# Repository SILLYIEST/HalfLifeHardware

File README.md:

# Heartbie

Mini pet that you can interact with! 
(Based off of the starter project Starbie)

This was so fun to create! I love doing personal projects (despite having no prior experience here T-T)

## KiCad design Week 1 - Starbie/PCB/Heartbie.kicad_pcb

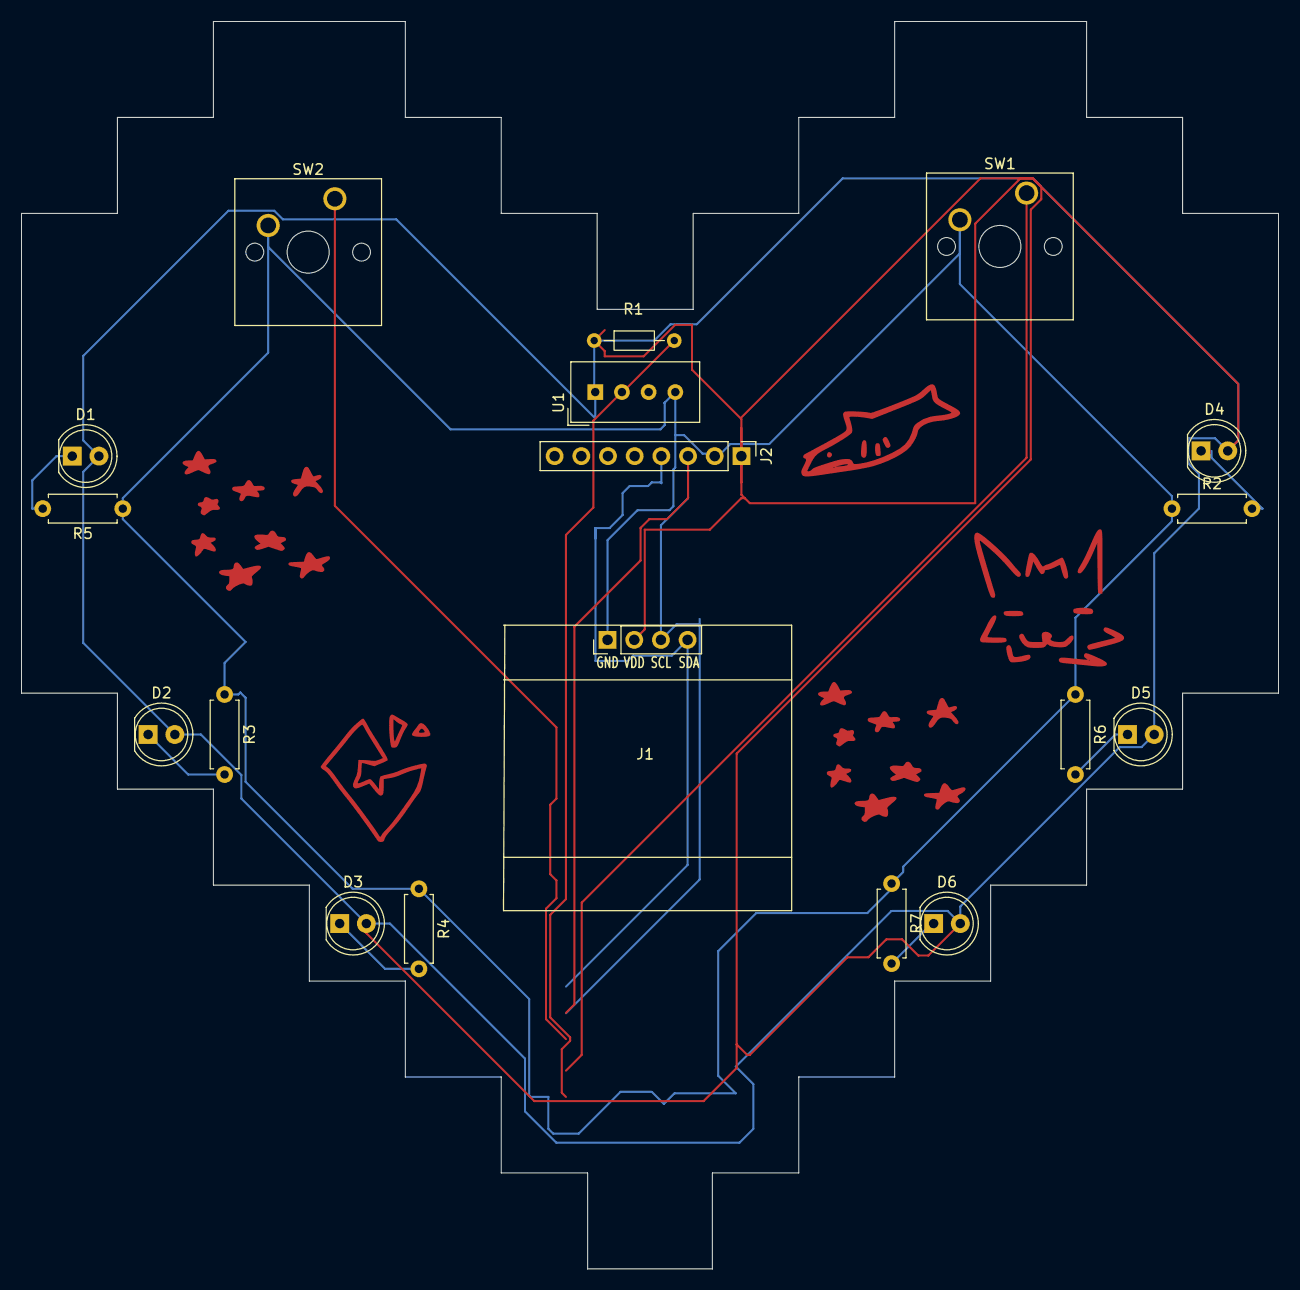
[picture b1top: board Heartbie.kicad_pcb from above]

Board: 2 copper layers, 119.7 x 118.8 mm, 19 parts (1 on the bottom side), 11 nets.

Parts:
D1, D2, D3, D4, D5, D6: LED; LED_D5.0mm
J1: Conn_01x04_Pin; Display_128x64_096_I2C
J2: Conn_01x08_Pin; PinHeader_1x08_P2.54mm_Vertical
R1: 10K; R_Axial_DIN0204_L3.6mm_D1.6mm_P7.62mm_Horizontal
R2, R3, R4, R5, R6, R7: R; R_Axial_DIN0207_L6.3mm_D2.5mm_P7.62mm_Horizontal
SW1, SW2: SW_Push; SW_Cherry_MX_1.00u_PCB
U1: DHT11; Aosong_DHT11_5.5x12.0_P2.54mm
U2: XIAO-ESP32-C3-SMD

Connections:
+3.3V: D1.2 (A), D2.2 (A), D3.2 (A), D4.2 (A), D5.2 (A), D6.2 (A), J1.2, J2.1, R1.1, U1.1 (VDD), U2.12 (3V3_OUT)
/DHT11 DATA: R1.2, U1.2 (DATA)
/SCL: J1.3, J2.3, U2.5 (D4)
/SDA: J1.4, J2.4, U2.6 (D5)
GND: J1.1, J2.2, R2.1, R3.1, R4.1, R5.1, R6.1, R7.1, SW1.2, SW2.2, U1.4 (GND), U2.13 (GND), U2.18 (GND)
unnamed: D1.1 (K), R5.2
unnamed: D2.1 (K), R3.2
unnamed: D3.1 (K), R4.2
unnamed: D4.1 (K), R2.2
unnamed: D5.1 (K), R6.2
unnamed: D6.1 (K), R7.2
